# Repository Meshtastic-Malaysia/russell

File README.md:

# Russell

Russell is a board designed to mount on an ER34615/IFR32700 cell and go Up! on a balloon.

- RAK3172 STM32WLE5CCU6 MCU + integrated SX1262 LoRa
- CDtop CD-PA1010D GPS
- Bosch Sensortec BME280 sensor
- Consonance CN3158 LiFePO4 solar charger

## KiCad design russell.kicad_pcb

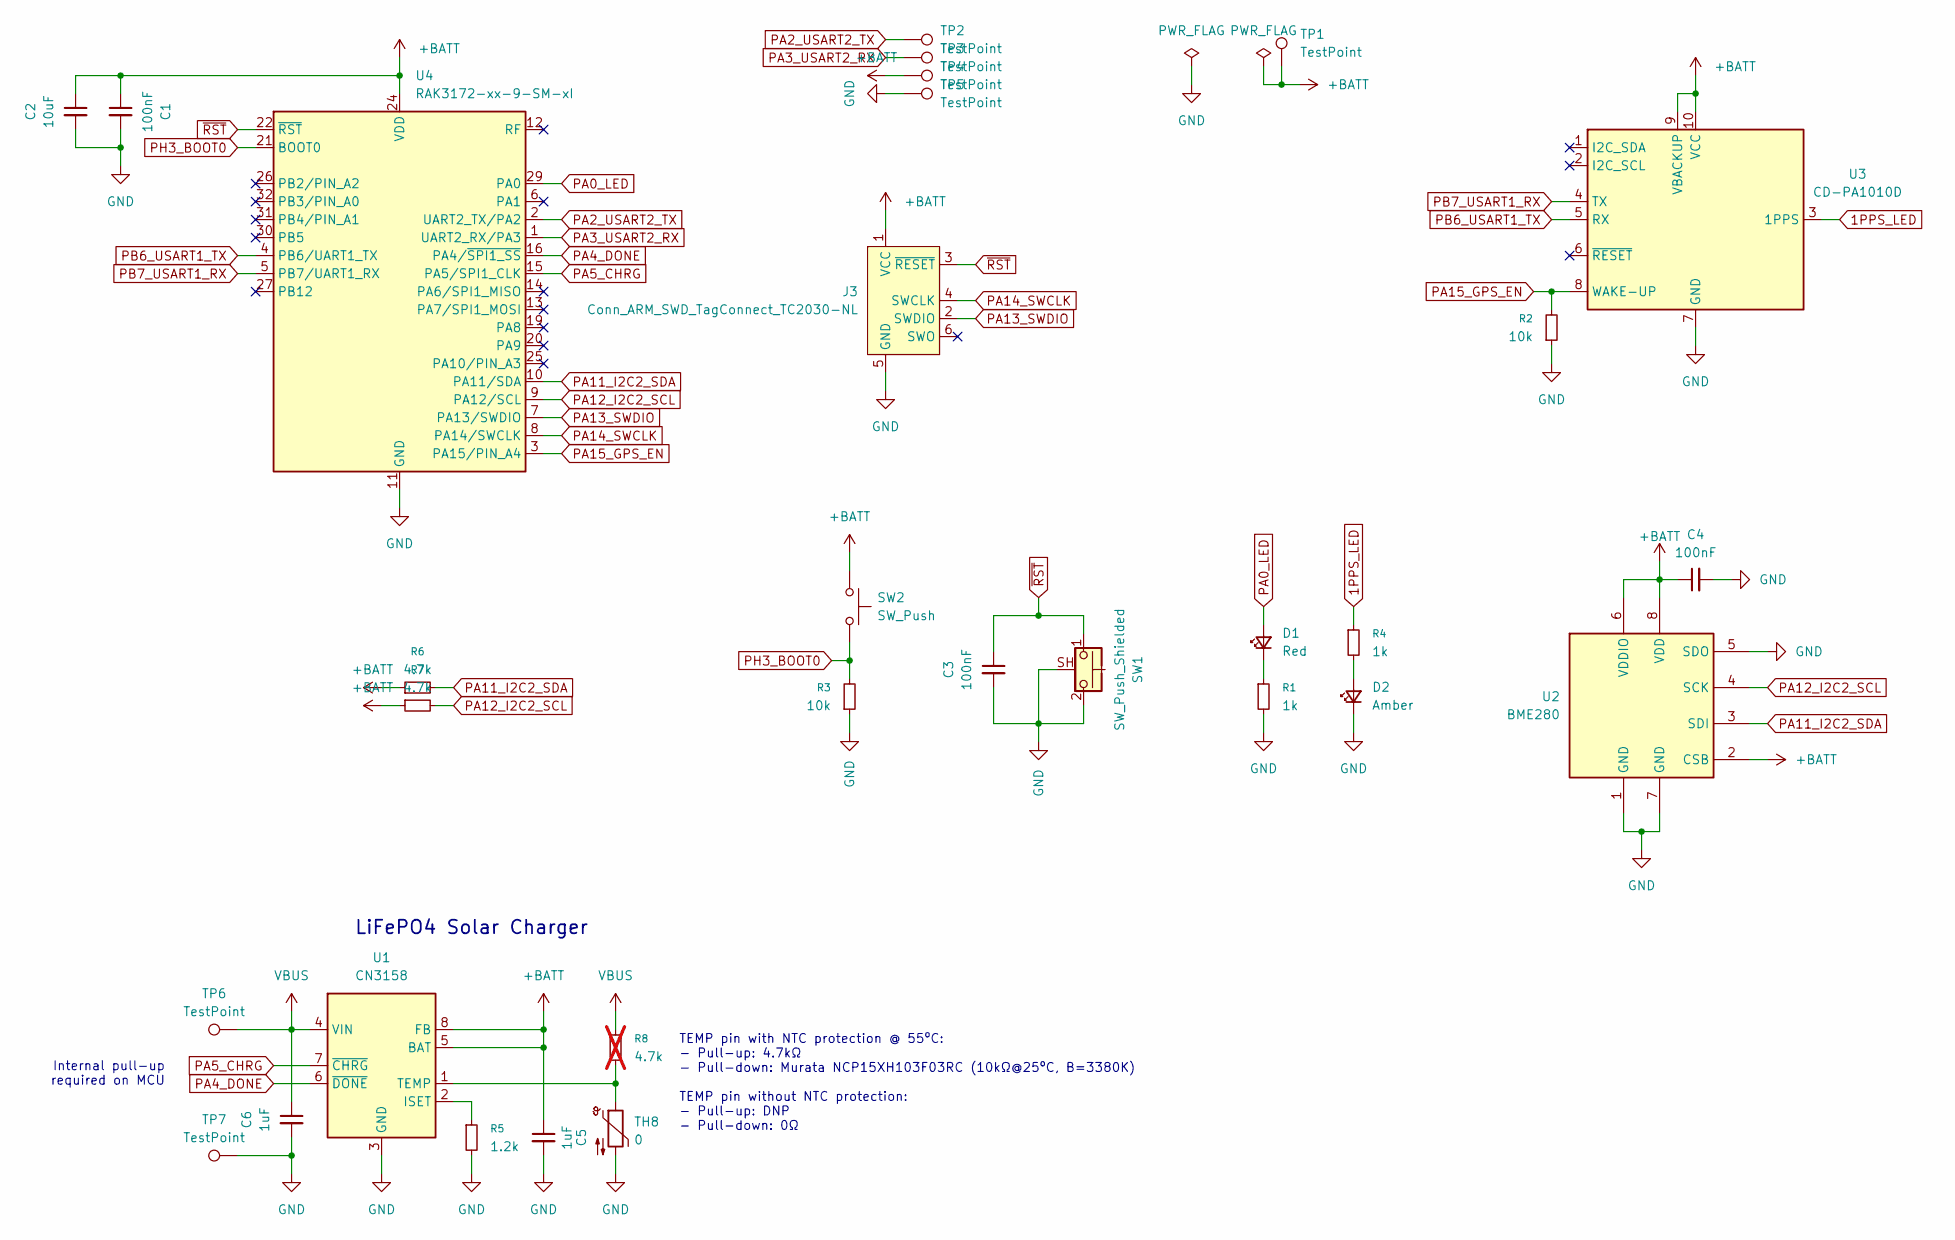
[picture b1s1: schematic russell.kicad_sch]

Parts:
C1, C3, C4: 100nF; C_0402_1005Metric; LCSC C1525
C2: 10uF; C_0402_1005Metric; LCSC C15525
C5: 1uF; LCSC C52923
C6: 1uF; C_0402_1005Metric; LCSC C52923
D1: Red; LED_0603_1608Metric; LCSC C2286
D2: Amber; LED_0603_1608Metric; LCSC C89811
J3: Conn_ARM_SWD_TagConnect_TC2030-NL; Tag-Connect_TC2030-IDC-NL_2x03_P1.27mm_Vertical
R1, R4: 1k; R_0402_1005Metric; LCSC C11702
R2, R3: 10k; R_0402_1005Metric; LCSC C25744
R5: 1.2k; R_0402_1005Metric; LCSC C25862
R6, R7: 4.7k; R_0402_1005Metric; LCSC C25900
R8: 4.7k; R_0402_1005Metric; LCSC C25900; not fitted
SW1: SW_Push_Shielded; SW_SPST_Shouhan_TS24CA; LCSC C5373430
SW2: SW_Push; SW_SPST_TS-1088-xR020; LCSC C720477
TH8: 0; R_0402_1005Metric; LCSC C17168
TP1: TestPoint; TestPoint_Pad_D4.0mm
TP2, TP3, TP5, TP7: TestPoint; TestPoint_Pad_D1.0mm
TP4, TP6: TestPoint; TestPoint_Pad_1.0x1.0mm
U1: CN3158; SOIC-8-1EP_3.9x4.9mm_P1.27mm_EP2.41x3.3mm_ThermalVias; LCSC C559032
U2: BME280; Bosch_LGA-8_2.5x2.5mm_P0.65mm_ClockwisePinNumbering; LCSC C92489
U3: CD-PA1010D; CDTop_CD-PA1010; LCSC C9900050424
U4: RAK3172-xx-9-SM-xI; RAK3172; LCSC C19723909

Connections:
1PPS_LED: R4.1, U3.3 (1PPS)
+BATT: C1.1, C2.1, C4.1, C5.1, J3.1 (VCC), R6.1, R7.1, SW2.1, TP1.1, TP4.1, U1.5 (BAT), U1.8 (FB), U2.2 (CSB), U2.6 (VDDIO), U2.8 (VDD), U3.9 (VBACKUP), U3.10 (VCC), U4.24 (VDD)
GND: C1.2, C2.2, C3.2, C4.2, C5.2, C6.2, D2.1 (K), J3.5 (GND), R1.2, R2.1, R3.1, R5.2, SW1.2, SW1.SH (B), TH8.2, TP5.1, TP7.1, U1.3 (GND), U1.9 (GND), U2.1 (GND), U2.5 (SDO), U2.7 (GND), U3.7 (GND), U4.11 (GND), U4.17 (GND), U4.18 (GND), U4.23 (GND), U4.28 (GND)
unnamed: D1.1 (K), R1.1
unnamed: D2.2 (A), R4.2
unnamed: R5.1, U1.2 (ISET)
unnamed: R8.2, TH8.1, U1.1 (TEMP)
PA0_LED: D1.2 (A), U4.29 (PA0)
PA2_USART2_TX: TP2.1, U4.2 (UART2_TX/PA2)
PA3_USART2_RX: TP3.1, U4.1 (UART2_RX/PA3)
PA4_DONE: U1.6 (~DONE), U4.16 (PA4/~SPI1_SS)
PA5_CHRG: U1.7 (~CHRG), U4.15 (PA5/SPI1_CLK)
PA11_I2C2_SDA: R6.2, U2.3 (SDI), U4.10 (PA11/SDA)
PA12_I2C2_SCL: R7.2, U2.4 (SCK), U4.9 (PA12/SCL)
PA13_SWDIO: J3.2 (SWDIO), U4.7 (PA13/SWDIO)
PA14_SWCLK: J3.4 (SWCLK), U4.8 (PA14/SWCLK)
PA15_GPS_EN: R2.2, U3.8 (WAKE-UP), U4.3 (PA15/PIN_A4)
PB6_USART1_TX: U3.5 (RX), U4.4 (PB6/UART1_TX)
PB7_USART1_RX: U3.4 (TX), U4.5 (PB7/UART1_RX)
PH3_BOOT0: R3.2, SW2.2, U4.21 (BOOT0)
VBUS: C6.1, R8.1, TP6.1, U1.4 (VIN)
~RST: C3.1, J3.3 (~RESET), SW1.1, U4.22 (~RST)

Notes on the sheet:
Internal pull-up required on MCU
LiFePO4 Solar Charger
TEMP pin with NTC protection @ 55ºC: - Pull-up: 4.7kΩ - Pull-down: Murata NCP15XH103F03RC (10kΩ@25ºC, B=3380K) TEMP pin without NTC protection: - Pull-up: DNP - Pull-down: 0Ω

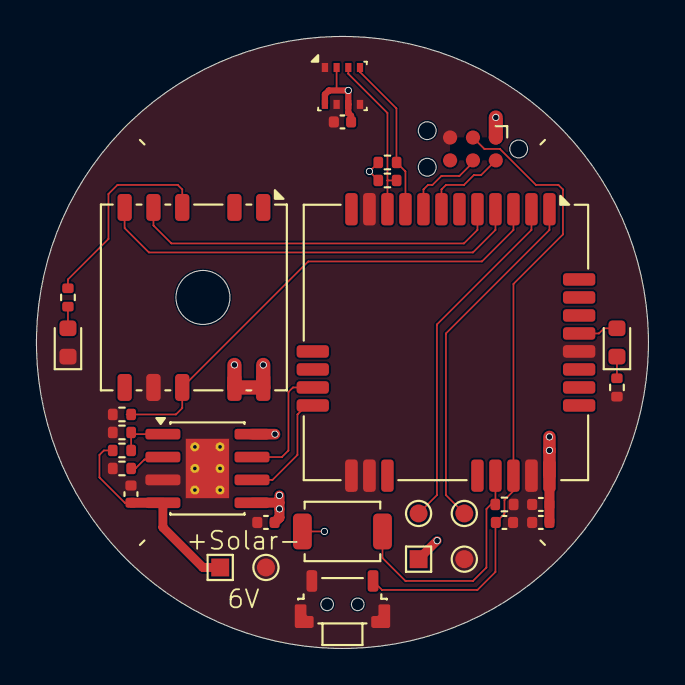
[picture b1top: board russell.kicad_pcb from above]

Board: 2 copper layers, 34.0 x 34.0 mm, 31 parts (1 on the bottom side), 22 nets.
